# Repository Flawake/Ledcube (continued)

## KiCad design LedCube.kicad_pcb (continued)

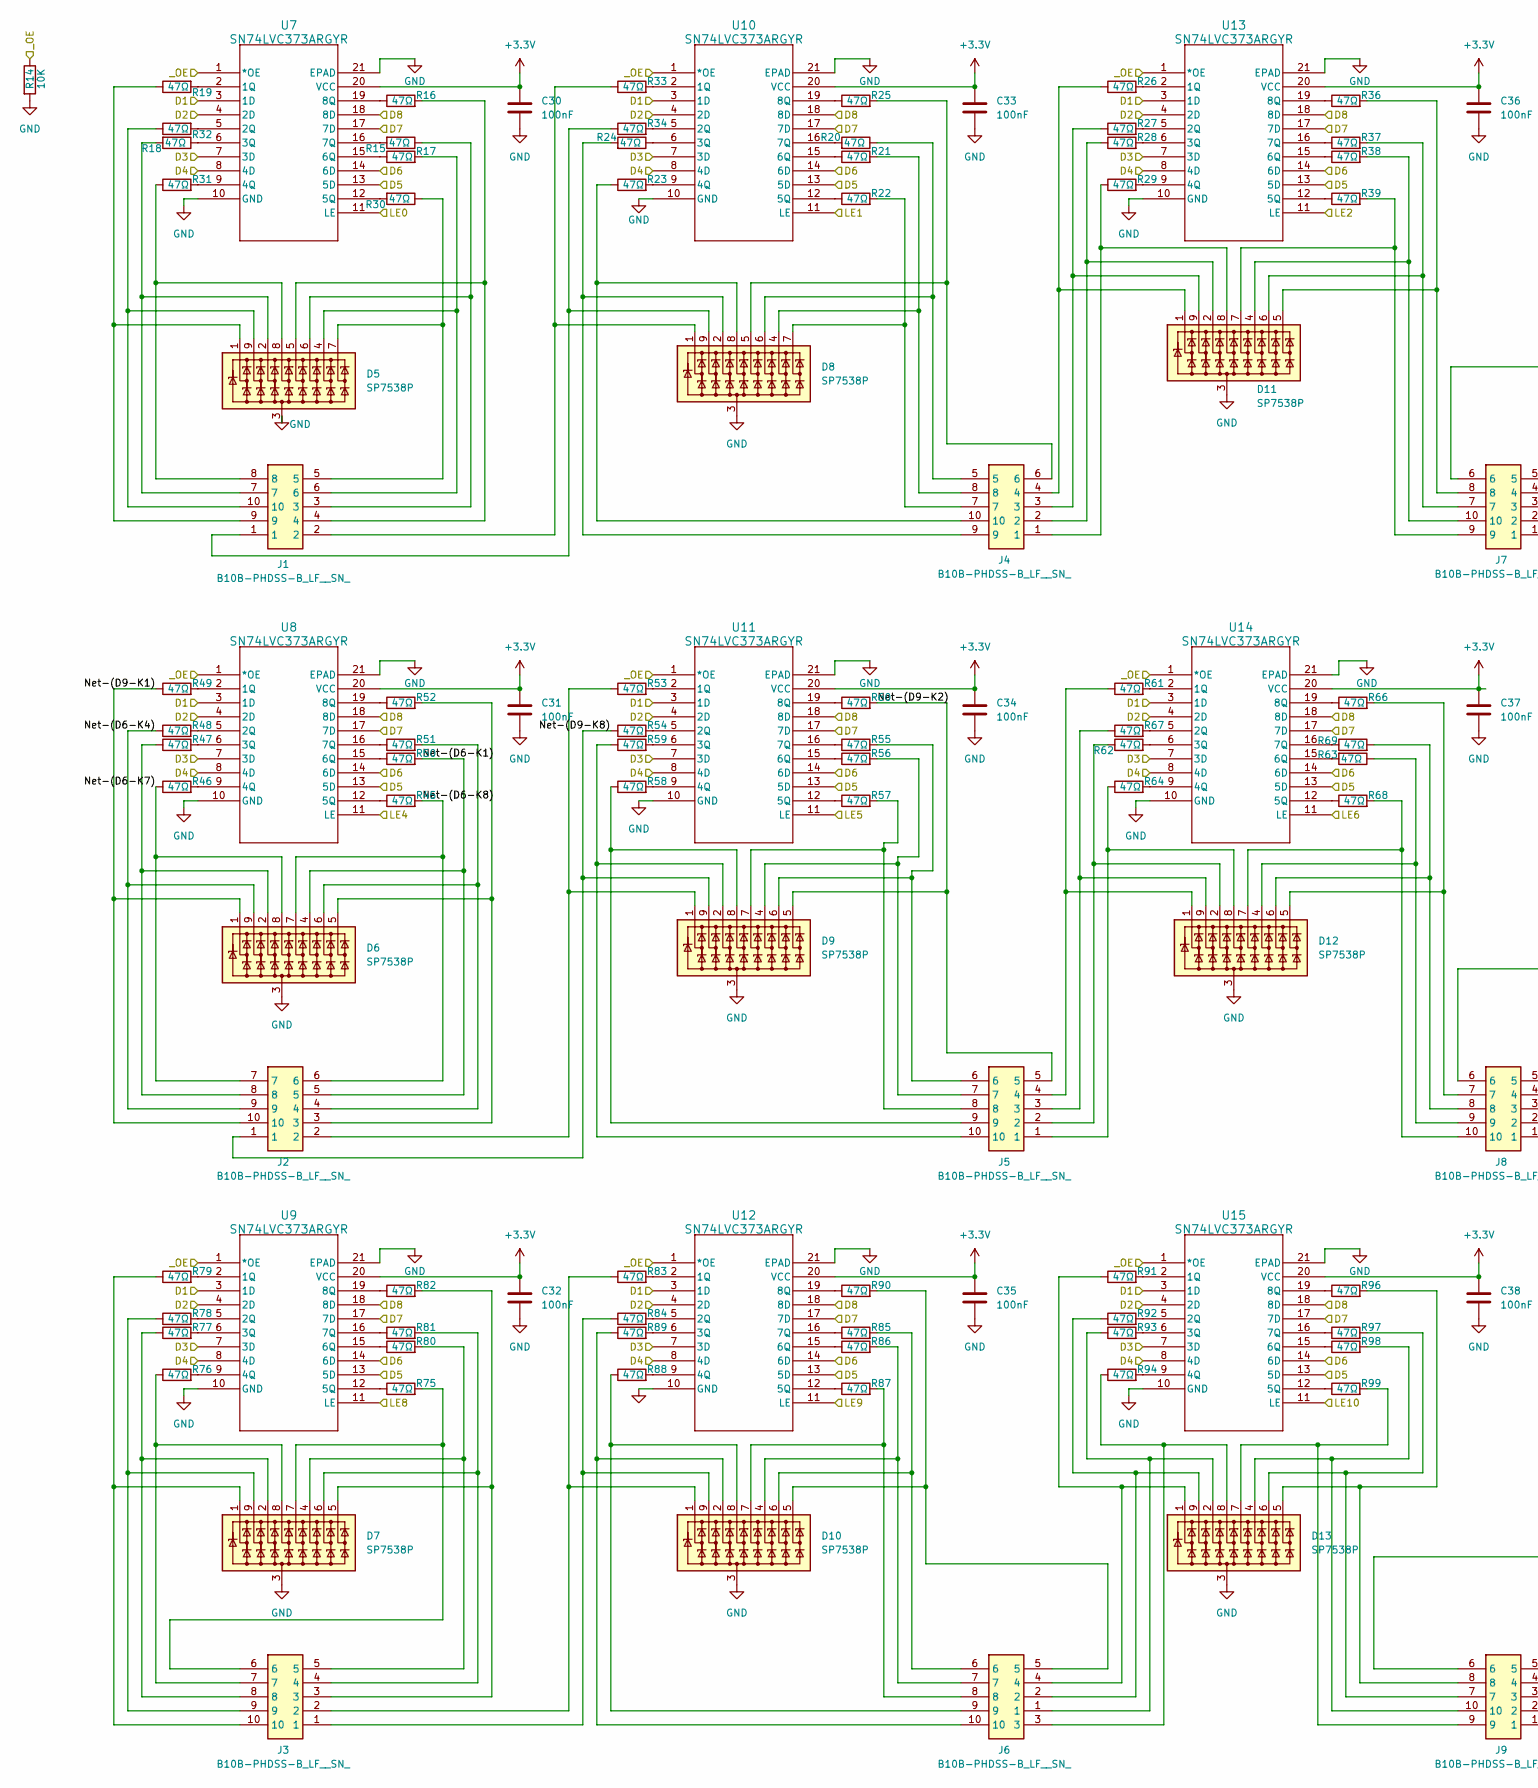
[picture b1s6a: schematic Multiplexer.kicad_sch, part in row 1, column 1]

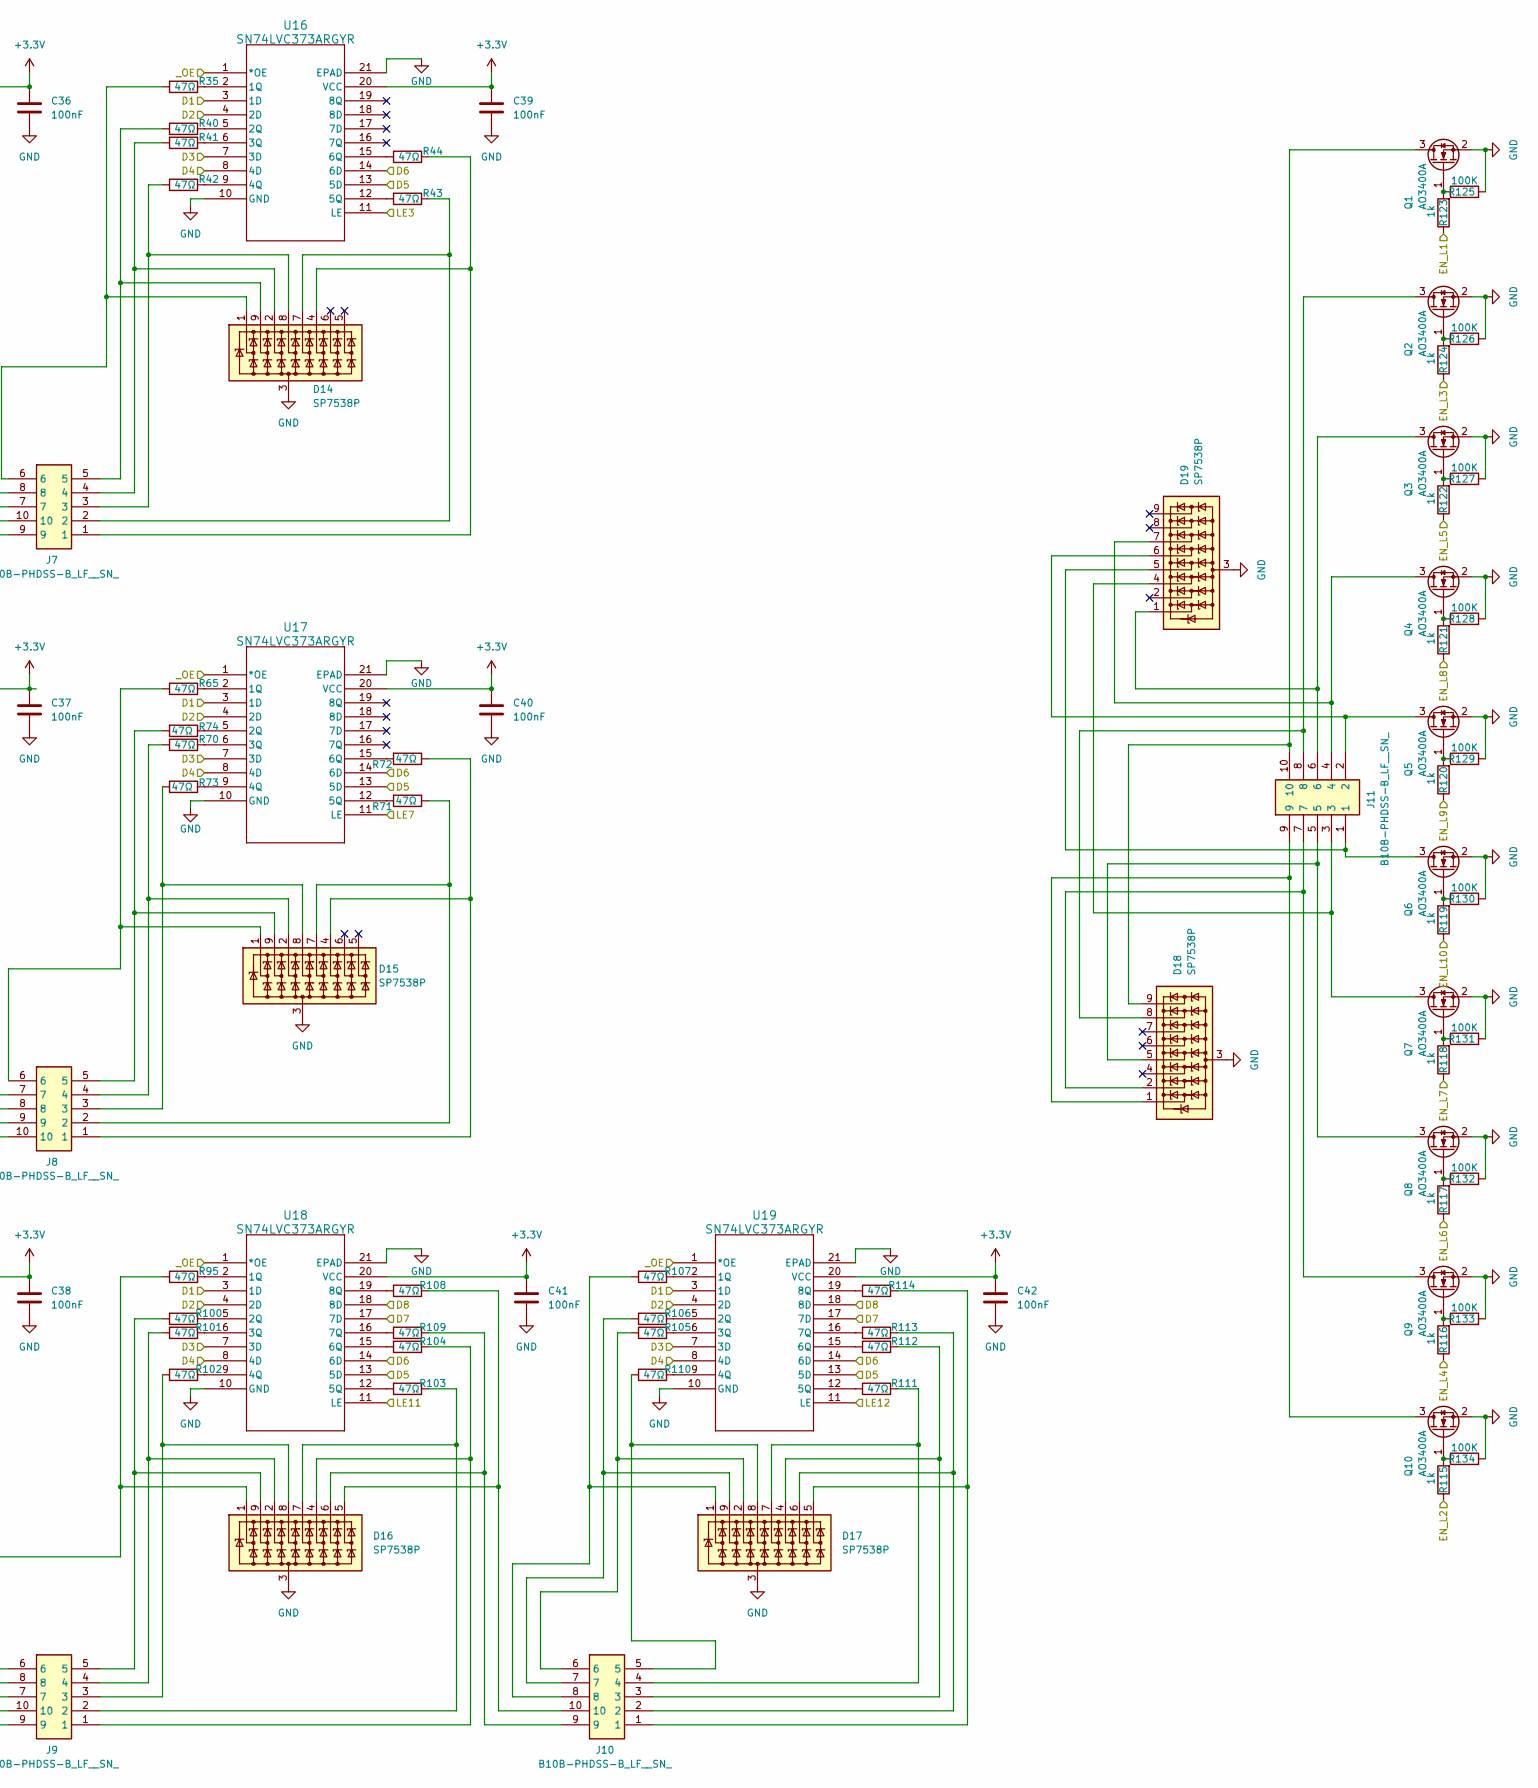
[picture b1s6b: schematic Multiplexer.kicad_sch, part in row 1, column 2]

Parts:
C30, C31, C32, C33, C34, C35, C36, C37, C38, C39, C40, C41, C42: 100nF; C_0603_1608Metric; LCSC C282519
D5, D6, D7, D8, D9, D10, D11, D12, D13, D14, D15, D16, D17, D18, D19: SP7538P; UDFN-9_1.0x3.8mm_P0.5mm
J1, J2, J3, J4, J5, J6, J7, J8, J9, J10, J11: B10B-PHDSS-B_LF__SN_; B10BPHDSSBLFSN; Mouser Part Number 306-B10BPHDSSBLFSN
Q1, Q2, Q3, Q4, Q5, Q6, Q7, Q8, Q9, Q10: AO3400A; SOT-23
R14: 10K; R_0603_1608Metric; LCSC C25804
R15, R16, R17, R18, R19, R20, R21, R22, R23, R24, R25, R26, R27, R28, R29, R30, R31, R32, R33, R34, R35, R36, R37, R38, R39, R40, R41, R42, R43, R44, R45, R46, R47, R48, R49, R50, R51, R52, R53, R54, R55, R56, R57, R58, R59, R60, R61, R62, R63, R64, R65, R66, R67, R68, R69, R70, R71, R72, R73, R74, R75, R76, R77, R78, R79, R80, R81, R82, R83, R84, R85, R86, R87, R88, R89, R90, R91, R92, R93, R94, R95, R96, R97, R98, R99, R100, R101, R102, R103, R104, R105, R106, R107, R108, R109, R110, R111, R112, R113, R114: 47Ω; R_0603_1608Metric; LCSC C23182
R115, R116, R117, R118, R119, R120, R121, R122, R123, R124: 1k; R_0603_1608Metric; LCSC C22548
R125, R126, R127, R128, R129, R130, R131, R132, R133, R134: 100K; R_0603_1608Metric; LCSC C25803
U7, U8, U9, U10, U11, U12, U13, U14, U15, U16, U17, U18, U19: SN74LVC373ARGYR; RGY20_3P05X2P05

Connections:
+3.3V: C30.1, C31.1, C32.1, C33.1, C34.1, C35.1, C36.1, C37.1, C38.1, C39.1, C40.1, C41.1, C42.1, U7.20 (VCC), U8.20 (VCC), U9.20 (VCC), U10.20 (VCC), U11.20 (VCC), U12.20 (VCC), U13.20 (VCC), U14.20 (VCC), U15.20 (VCC), U16.20 (VCC), U17.20 (VCC), U18.20 (VCC), U19.20 (VCC); also elsewhere on the board
/Core/D1: U7.3 (1D), U8.3 (1D), U9.3 (1D), U10.3 (1D), U11.3 (1D), U12.3 (1D), U13.3 (1D), U14.3 (1D), U15.3 (1D), U16.3 (1D), U17.3 (1D), U18.3 (1D), U19.3 (1D); also elsewhere on the board
/Core/D2: U7.4 (2D), U8.4 (2D), U9.4 (2D), U10.4 (2D), U11.4 (2D), U12.4 (2D), U13.4 (2D), U14.4 (2D), U15.4 (2D), U16.4 (2D), U17.4 (2D), U18.4 (2D), U19.4 (2D); also elsewhere on the board
/Core/D3: U7.7 (3D), U8.7 (3D), U9.7 (3D), U10.7 (3D), U11.7 (3D), U12.7 (3D), U13.7 (3D), U14.7 (3D), U15.7 (3D), U16.7 (3D), U17.7 (3D), U18.7 (3D), U19.7 (3D); also elsewhere on the board
/Core/D4: U7.8 (4D), U8.8 (4D), U9.8 (4D), U10.8 (4D), U11.8 (4D), U12.8 (4D), U13.8 (4D), U14.8 (4D), U15.8 (4D), U16.8 (4D), U17.8 (4D), U18.8 (4D), U19.8 (4D); also elsewhere on the board
/Core/D5: U7.13 (5D), U8.13 (5D), U9.13 (5D), U10.13 (5D), U11.13 (5D), U12.13 (5D), U13.13 (5D), U14.13 (5D), U15.13 (5D), U16.13 (5D), U17.13 (5D), U18.13 (5D), U19.13 (5D); also elsewhere on the board
/Core/D6: U7.14 (6D), U8.14 (6D), U9.14 (6D), U10.14 (6D), U11.14 (6D), U12.14 (6D), U13.14 (6D), U14.14 (6D), U15.14 (6D), U16.14 (6D), U17.14 (6D), U18.14 (6D), U19.14 (6D); also elsewhere on the board
/Core/D7: U7.17 (7D), U8.17 (7D), U9.17 (7D), U10.17 (7D), U11.17 (7D), U12.17 (7D), U13.17 (7D), U14.17 (7D), U15.17 (7D), U18.17 (7D), U19.17 (7D); also elsewhere on the board
/Core/D8: U7.18 (8D), U8.18 (8D), U9.18 (8D), U10.18 (8D), U11.18 (8D), U12.18 (8D), U13.18 (8D), U14.18 (8D), U15.18 (8D), U18.18 (8D), U19.18 (8D); also elsewhere on the board
/Core/EN_L1: R123.1; also elsewhere on the board
/Core/EN_L2: R115.1; also elsewhere on the board
/Core/EN_L3: R124.1; also elsewhere on the board
/Core/EN_L4: R116.1; also elsewhere on the board
/Core/EN_L5: R122.1; also elsewhere on the board
/Core/EN_L6: R117.1; also elsewhere on the board
/Core/EN_L7: R118.1; also elsewhere on the board
/Core/EN_L8: R121.1; also elsewhere on the board
/Core/EN_L9: R120.1; also elsewhere on the board
/Core/EN_L10: R119.1; also elsewhere on the board
/Core/LE0: U7.11 (LE); also elsewhere on the board
/Core/LE1: U10.11 (LE); also elsewhere on the board
/Core/LE2: U13.11 (LE); also elsewhere on the board
/Core/LE3: U16.11 (LE); also elsewhere on the board
/Core/LE4: U8.11 (LE); also elsewhere on the board
/Core/LE5: U11.11 (LE); also elsewhere on the board
/Core/LE6: U14.11 (LE); also elsewhere on the board
/Core/LE7: U17.11 (LE); also elsewhere on the board
/Core/LE8: U9.11 (LE); also elsewhere on the board
/Core/LE9: U12.11 (LE); also elsewhere on the board
/Core/LE10: U15.11 (LE); also elsewhere on the board
/Core/LE11: U18.11 (LE); also elsewhere on the board
/Core/LE12: U19.11 (LE); also elsewhere on the board
/Core/_OE: R14.1, U7.1 (*OE), U8.1 (*OE), U9.1 (*OE), U10.1 (*OE), U11.1 (*OE), U12.1 (*OE), U13.1 (*OE), U14.1 (*OE), U15.1 (*OE), U16.1 (*OE), U17.1 (*OE), U18.1 (*OE), U19.1 (*OE); also elsewhere on the board
/Multiplexer/Net-(D6-K1): D6.4 (K3), J2.5, R50.2
/Multiplexer/Net-(D6-K4): D6.9 (K8), J2.9, R48.1
/Multiplexer/Net-(D6-K7): D6.8 (K7), J2.7, R46.1
/Multiplexer/Net-(D6-K8): D6.7 (K6), J2.6, R45.2
/Multiplexer/Net-(D9-K1): D6.1 (K1), J2.10, R49.1
/Multiplexer/Net-(D9-K2): D9.5 (K4), J5.5, R60.2
/Multiplexer/Net-(D9-K8): D9.9 (K8), J2.1, R54.1
GND: C30.2, C31.2, C32.2, C33.2, C34.2, C35.2, C36.2, C37.2, C38.2, C39.2, C40.2, C41.2, C42.2, D5.3 (A), D6.3 (A), D7.3 (A), D8.3 (A), D9.3 (A), D10.3 (A), D11.3 (A), D12.3 (A), D13.3 (A), D14.3 (A), D15.3 (A), D16.3 (A), D17.3 (A), D18.3 (A), D19.3 (A), Q1.2 (S), Q2.2 (S), Q3.2 (S), Q4.2 (S), Q5.2 (S), Q6.2 (S), Q7.2 (S), Q8.2 (S), Q9.2 (S), Q10.2 (S), R14.2, R125.2, R126.2, R127.2, R128.2, R129.2, R130.2, R131.2, R132.2, R133.2, R134.2, U7.10 (GND), U7.21 (EPAD), U8.10 (GND), U8.21 (EPAD), U9.10 (GND), U9.21 (EPAD), U10.10 (GND), U10.21 (EPAD), U11.10 (GND), U11.21 (EPAD), U12.10 (GND), U12.21 (EPAD), U13.10 (GND), U13.21 (EPAD), U14.10 (GND), U14.21 (EPAD), U15.10 (GND), U15.21 (EPAD), U16.10 (GND), U16.21 (EPAD), U17.10 (GND), U17.21 (EPAD), U18.10 (GND), U18.21 (EPAD), U19.10 (GND), U19.21 (EPAD); also elsewhere on the board
unnamed: D5.1 (K1), J1.9, R19.1
unnamed: D5.2 (K2), J1.7, R18.2
unnamed: D5.4 (K3), J1.6, R17.2
unnamed: D5.5 (K4), J1.4, R16.2
unnamed: D5.6 (K5), J1.3, R15.1
unnamed: D5.7 (K6), J1.5, R30.1
unnamed: D5.8 (K7), J1.8, R31.1
unnamed: D5.9 (K8), J1.10, R32.1
unnamed: D6.2 (K2), J2.8, R47.1
unnamed: D6.5 (K4), J2.3, R52.2
unnamed: D6.6 (K5), J2.4, R51.2
unnamed: D7.1 (K1), J3.10, R79.1
unnamed: D7.2 (K2), J3.8, R77.1
unnamed: D7.4 (K3), J3.5, R80.2
unnamed: D7.5 (K4), J3.3, R82.2
unnamed: D7.6 (K5), J3.4, R81.2
unnamed: D7.7 (K6), J3.6, R75.2
unnamed: D7.8 (K7), J3.7, R76.1
unnamed: D7.9 (K8), J3.9, R78.1
unnamed: D8.1 (K1), J1.2, R33.1
unnamed: D8.2 (K2), J4.9, R24.2
unnamed: D8.4 (K3), J4.8, R21.2
unnamed: D8.5 (K4), J4.6, R25.2
unnamed: D8.6 (K5), J4.5, R20.1
unnamed: D8.7 (K6), J4.7, R22.2
unnamed: D8.8 (K7), J4.10, R23.1
unnamed: D8.9 (K8), J1.1, R34.1
unnamed: D9.1 (K1), J2.2, R53.1
unnamed: D9.2 (K2), J5.10, R59.1
unnamed: D9.4 (K3), J5.7, R56.2
unnamed: D9.6 (K5), J5.6, R55.2
unnamed: D9.7 (K6), J5.8, R57.2
unnamed: D9.8 (K7), J5.9, R58.1
unnamed: D10.1 (K1), J3.2, R83.1
unnamed: D10.2 (K2), J6.10, R89.1
unnamed: D10.4 (K3), J6.7, R86.2
unnamed: D10.5 (K4), J6.5, R90.2
unnamed: D10.6 (K5), J6.6, R85.2
unnamed: D10.7 (K6), J6.8, R87.2
unnamed: D10.8 (K7), J6.9, R88.1
unnamed: D10.9 (K8), J3.1, R84.1
unnamed: D11.1 (K1), J4.4, R26.1
unnamed: D11.2 (K2), J4.2, R28.1
unnamed: D11.4 (K3), J7.10, R38.2
unnamed: D11.5 (K4), J7.8, R36.2
unnamed: D11.6 (K5), J7.7, R37.2
unnamed: D11.7 (K6), J7.9, R39.2
unnamed: D11.8 (K7), J4.1, R29.1
unnamed: D11.9 (K8), J4.3, R27.1
unnamed: D12.1 (K1), J5.4, R61.1
unnamed: D12.2 (K2), J5.2, R62.1
unnamed: D12.4 (K3), J8.9, R63.1
unnamed: D12.5 (K4), J8.7, R66.2
unnamed: D12.6 (K5), J8.8, R69.2
unnamed: D12.7 (K6), J8.10, R68.2
unnamed: D12.8 (K7), J5.1, R64.1
unnamed: D12.9 (K8), J5.3, R67.1
unnamed: D13.1 (K1), J6.4, R91.1
unnamed: D13.2 (K2), J6.1, R93.1
unnamed: D13.4 (K3), J9.10, R98.2
unnamed: D13.5 (K4), J9.8, R96.2
unnamed: D13.6 (K5), J9.7, R97.2
unnamed: D13.7 (K6), J9.9, R99.2
unnamed: D13.8 (K7), J6.3, R94.1
unnamed: D13.9 (K8), J6.2, R92.1
unnamed: D14.1 (K1), J7.6, R35.1
unnamed: D14.2 (K2), J7.4, R41.1
unnamed: D14.4 (K3), J7.1, R44.2
unnamed: D14.7 (K6), J7.2, R43.2
unnamed: D14.8 (K7), J7.3, R42.1
unnamed: D14.9 (K8), J7.5, R40.1
unnamed: D15.1 (K1), J8.6, R65.1
unnamed: D15.2 (K2), J8.4, R70.1
unnamed: D15.4 (K3), J8.1, R72.1
unnamed: D15.7 (K6), J8.2, R71.1
unnamed: D15.8 (K7), J8.3, R73.2
unnamed: D15.9 (K8), J8.5, R74.2
unnamed: D16.1 (K1), J9.6, R95.1
unnamed: D16.2 (K2), J9.4, R101.1
unnamed: D16.4 (K3), J9.1, R104.2
unnamed: D16.5 (K4), J10.10, R108.2
unnamed: D16.6 (K5), J10.9, R109.2
unnamed: D16.7 (K6), J9.2, R103.2
unnamed: D16.8 (K7), J9.3, R102.1
unnamed: D16.9 (K8), J9.5, R100.1
unnamed: D17.1 (K1), J10.8, R107.1
unnamed: D17.2 (K2), J10.6, R105.1
unnamed: D17.4 (K3), J10.3, R112.2
unnamed: D17.5 (K4), J10.1, R114.2
unnamed: D17.6 (K5), J10.2, R113.2
unnamed: D17.7 (K6), J10.4, R111.2
unnamed: D17.8 (K7), J10.5, R110.1
unnamed: D17.9 (K8), J10.7, R106.1
unnamed: D18.1 (K1), J11.9, Q10.3 (D)
unnamed: D18.2 (K2), J11.7, Q9.3 (D)
unnamed: D18.5 (K4), J11.5, Q8.3 (D)
unnamed: D18.8 (K7), J11.8, Q2.3 (D)
unnamed: D18.9 (K8), J11.10, Q1.3 (D)
unnamed: D19.1 (K1), J11.6, Q3.3 (D)
unnamed: D19.4 (K3), J11.3, Q7.3 (D)
unnamed: D19.5 (K4), J11.1, Q6.3 (D)
unnamed: D19.6 (K5), J11.2, Q5.3 (D)
unnamed: D19.7 (K6), J11.4, Q4.3 (D)
unnamed: Q1.1 (G), R123.2, R125.1
unnamed: Q2.1 (G), R124.2, R126.1
unnamed: Q3.1 (G), R122.2, R127.1
unnamed: Q4.1 (G), R121.2, R128.1
unnamed: Q5.1 (G), R120.2, R129.1
unnamed: Q6.1 (G), R119.2, R130.1
unnamed: Q7.1 (G), R118.2, R131.1
unnamed: Q8.1 (G), R117.2, R132.1
unnamed: Q9.1 (G), R116.2, R133.1
unnamed: Q10.1 (G), R115.2, R134.1
unnamed: R19.2, U7.2 (1Q)
unnamed: R32.2, U7.5 (2Q)
unnamed: R18.1, U7.6 (3Q)
unnamed: R31.2, U7.9 (4Q)
unnamed: R30.2, U7.12 (5Q)
unnamed: R17.1, U7.15 (6Q)
unnamed: R15.2, U7.16 (7Q)
unnamed: R16.1, U7.19 (8Q)
unnamed: R49.2, U8.2 (1Q)
unnamed: R48.2, U8.5 (2Q)
unnamed: R47.2, U8.6 (3Q)
unnamed: R46.2, U8.9 (4Q)
unnamed: R45.1, U8.12 (5Q)
unnamed: R50.1, U8.15 (6Q)
unnamed: R51.1, U8.16 (7Q)
unnamed: R52.1, U8.19 (8Q)
unnamed: R79.2, U9.2 (1Q)
unnamed: R78.2, U9.5 (2Q)
unnamed: R77.2, U9.6 (3Q)
unnamed: R76.2, U9.9 (4Q)
unnamed: R75.1, U9.12 (5Q)
unnamed: R80.1, U9.15 (6Q)
unnamed: R81.1, U9.16 (7Q)
unnamed: R82.1, U9.19 (8Q)
unnamed: R33.2, U10.2 (1Q)
unnamed: R34.2, U10.5 (2Q)
unnamed: R24.1, U10.6 (3Q)
unnamed: R23.2, U10.9 (4Q)
unnamed: R22.1, U10.12 (5Q)
unnamed: R21.1, U10.15 (6Q)
unnamed: R20.2, U10.16 (7Q)
unnamed: R25.1, U10.19 (8Q)
unnamed: R53.2, U11.2 (1Q)
unnamed: R54.2, U11.5 (2Q)
unnamed: R59.2, U11.6 (3Q)
unnamed: R58.2, U11.9 (4Q)
unnamed: R57.1, U11.12 (5Q)
unnamed: R56.1, U11.15 (6Q)
unnamed: R55.1, U11.16 (7Q)
unnamed: R60.1, U11.19 (8Q)
unnamed: R83.2, U12.2 (1Q)
unnamed: R84.2, U12.5 (2Q)
unnamed: R89.2, U12.6 (3Q)
unnamed: R88.2, U12.9 (4Q)
unnamed: R87.1, U12.12 (5Q)
unnamed: R86.1, U12.15 (6Q)
unnamed: R85.1, U12.16 (7Q)
unnamed: R90.1, U12.19 (8Q)
unnamed: R26.2, U13.2 (1Q)
unnamed: R27.2, U13.5 (2Q)
unnamed: R28.2, U13.6 (3Q)
unnamed: R29.2, U13.9 (4Q)
unnamed: R39.1, U13.12 (5Q)
unnamed: R38.1, U13.15 (6Q)
unnamed: R37.1, U13.16 (7Q)
unnamed: R36.1, U13.19 (8Q)
unnamed: R61.2, U14.2 (1Q)
unnamed: R67.2, U14.5 (2Q)
unnamed: R62.2, U14.6 (3Q)
unnamed: R64.2, U14.9 (4Q)
unnamed: R68.1, U14.12 (5Q)
unnamed: R63.2, U14.15 (6Q)
unnamed: R69.1, U14.16 (7Q)
unnamed: R66.1, U14.19 (8Q)
unnamed: R91.2, U15.2 (1Q)
unnamed: R92.2, U15.5 (2Q)
unnamed: R93.2, U15.6 (3Q)
unnamed: R94.2, U15.9 (4Q)
unnamed: R99.1, U15.12 (5Q)
unnamed: R98.1, U15.15 (6Q)
unnamed: R97.1, U15.16 (7Q)
unnamed: R96.1, U15.19 (8Q)
unnamed: R35.2, U16.2 (1Q)
unnamed: R40.2, U16.5 (2Q)
unnamed: R41.2, U16.6 (3Q)
unnamed: R42.2, U16.9 (4Q)
unnamed: R43.1, U16.12 (5Q)
unnamed: R44.1, U16.15 (6Q)
unnamed: R65.2, U17.2 (1Q)
unnamed: R74.1, U17.5 (2Q)
unnamed: R70.2, U17.6 (3Q)
unnamed: R73.1, U17.9 (4Q)
unnamed: R71.2, U17.12 (5Q)
unnamed: R72.2, U17.15 (6Q)
unnamed: R95.2, U18.2 (1Q)
unnamed: R100.2, U18.5 (2Q)
unnamed: R101.2, U18.6 (3Q)
unnamed: R102.2, U18.9 (4Q)
unnamed: R103.1, U18.12 (5Q)
unnamed: R104.1, U18.15 (6Q)
unnamed: R109.1, U18.16 (7Q)
unnamed: R108.1, U18.19 (8Q)
unnamed: R107.2, U19.2 (1Q)
unnamed: R106.2, U19.5 (2Q)
unnamed: R105.2, U19.6 (3Q)
unnamed: R110.2, U19.9 (4Q)
unnamed: R111.1, U19.12 (5Q)
unnamed: R112.1, U19.15 (6Q)
unnamed: R113.1, U19.16 (7Q)
unnamed: R114.1, U19.19 (8Q)

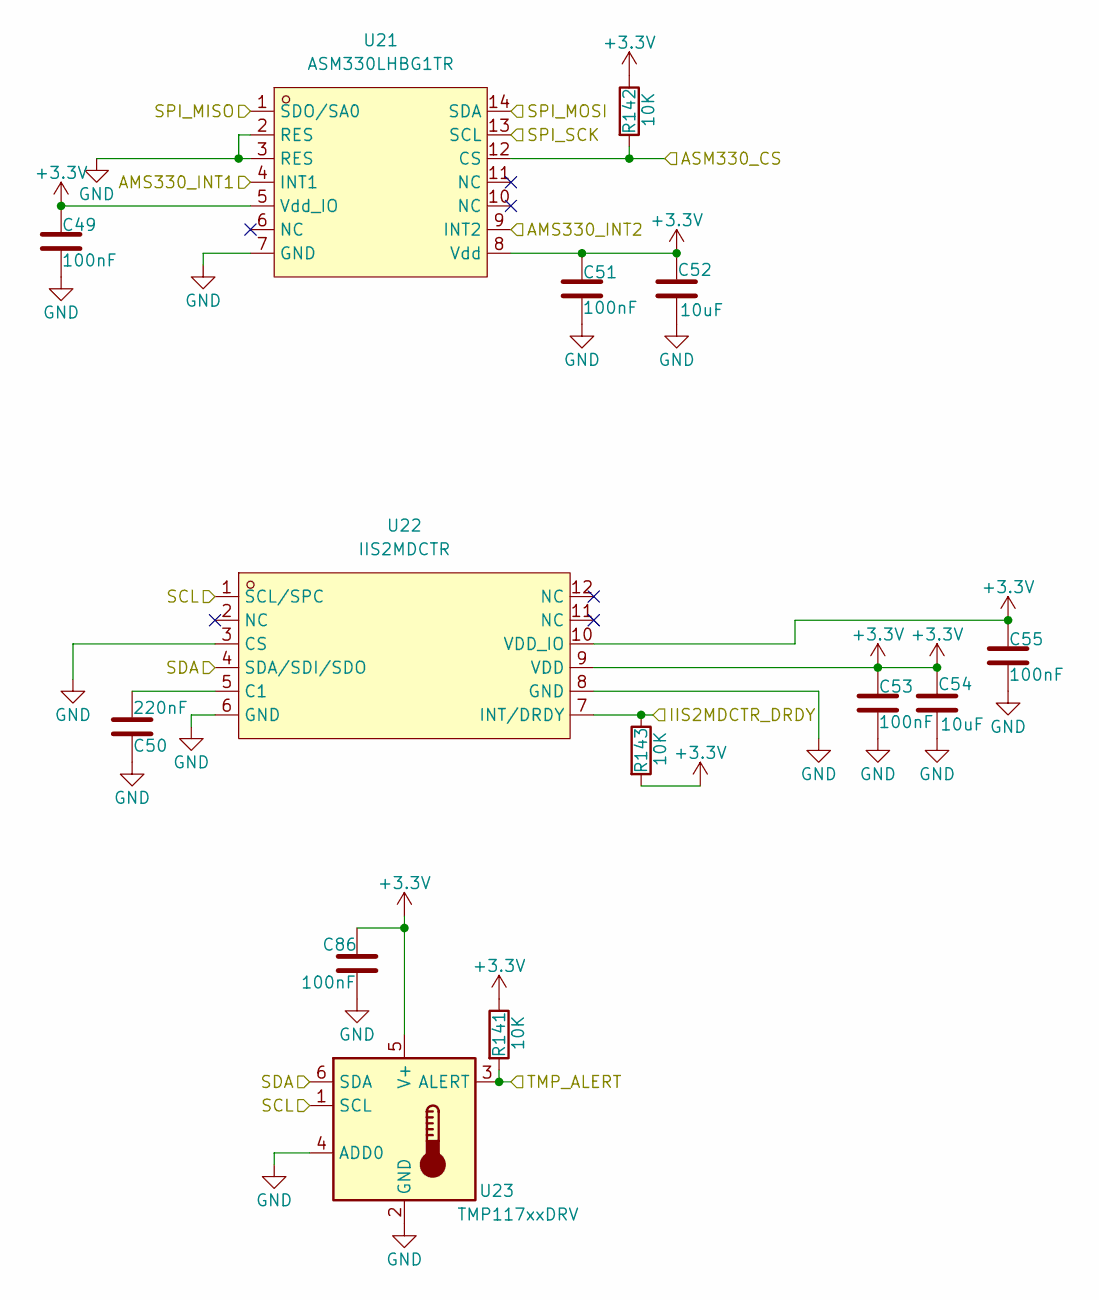
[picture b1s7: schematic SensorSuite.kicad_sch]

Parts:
C49, C51, C53, C55, C86: 100nF; C_0603_1608Metric; LCSC C282519
C50: 220nF; C_0402_1005Metric; LCSC C16772
C52, C54: 10uF; C_0805_2012Metric; LCSC C440198
R141, R142, R143: 10K; R_0603_1608Metric; LCSC C25804
U21: ASM330LHBG1TR; LGA-14_L3.0-W2.5-P0.50-BL; LCSC Part C22458556
U22: IIS2MDCTR; LGA-12_L2.0-W2.0-P0.50-TL; LCSC Part C2655002
U23: TMP117xxDRV; WSON-6-1EP_2x2mm_P0.65mm_EP1x1.6mm

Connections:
+3.3V: C49.1, C51.1, C52.1, C53.1, C54.1, C55.1, C86.1, R141.1, R142.1, R143.2, U21.5 (Vdd_IO), U21.8 (Vdd), U22.9 (VDD), U22.10 (VDD_IO), U23.5 (V+); also elsewhere on the board
/Core/AMS330_CS: R142.2, U21.12 (CS); also elsewhere on the board
/Core/AMS330_INT1: U21.4 (INT1); also elsewhere on the board
/Core/AMS330_INT2: U21.9 (INT2); also elsewhere on the board
/Core/I2C1_SCL: U22.1 (SCL/SPC), U23.1 (SCL); also elsewhere on the board
/Core/I2C1_SDA: U22.4 (SDA/SDI/SDO), U23.6 (SDA); also elsewhere on the board
/Core/IIS2MDCTR_DRDY: R143.1, U22.7 (INT/DRDY); also elsewhere on the board
/Core/SPI1_MISO: U21.1 (SDO/SA0); also elsewhere on the board
/Core/SPI1_MOSI: U21.14 (SDA); also elsewhere on the board
/Core/SPI1_SCK: U21.13 (SCL); also elsewhere on the board
/Core/TMP_ALERT: R141.2, U23.3 (ALERT); also elsewhere on the board
GND: C49.2, C50.2, C51.2, C52.2, C53.2, C54.2, C55.2, C86.2, U21.2 (RES), U21.3 (RES), U21.7 (GND), U22.3 (CS), U22.6 (GND), U22.8 (GND), U23.2 (GND), U23.4 (ADD0); also elsewhere on the board
unnamed: C50.1, U22.5 (C1)

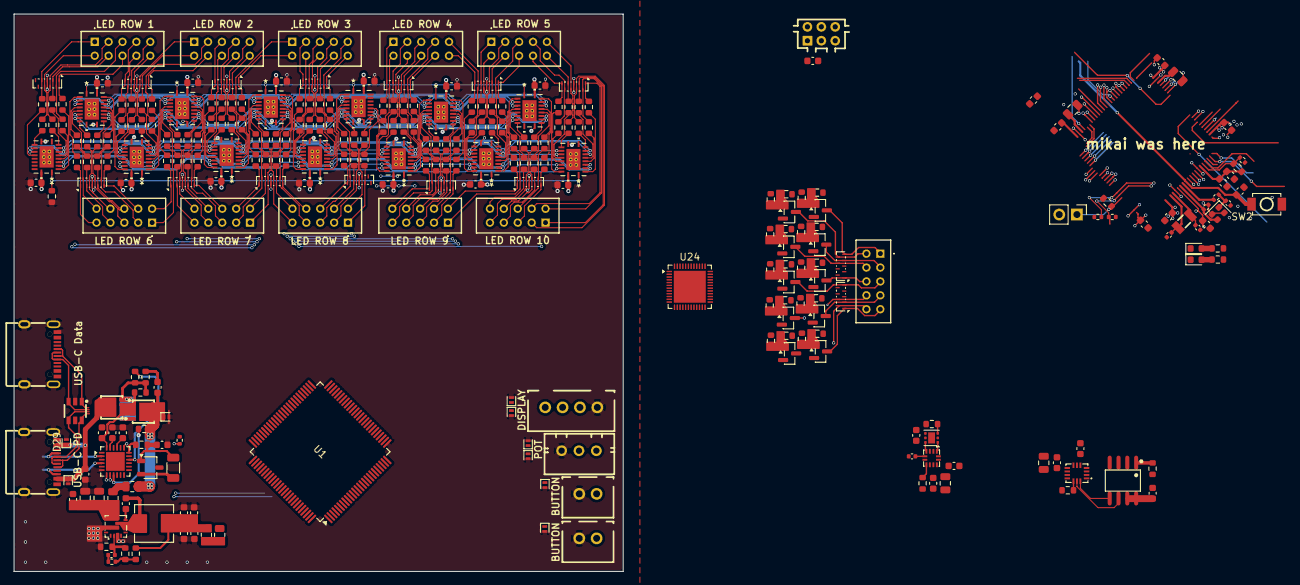
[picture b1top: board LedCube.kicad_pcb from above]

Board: 4 copper layers, 87.7 x 80.2 mm, 287 parts (1 on the bottom side), 315 nets.

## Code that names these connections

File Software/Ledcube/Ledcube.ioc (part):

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Mcu.Name=STM32H743VGTx
Mcu.Package=LQFP100
Mcu.UserName=STM32H743VGTx
PA0.GPIOParameters=GPIO_Label
PA0.GPIO_Label=GDO0_1
PA0.Signal=GPIO_Input
PA1.GPIOParameters=GPIO_Label
PA1.GPIO_Label=GDO2_1
PA1.Signal=GPIO_Input
PA10.GPIOParameters=GPIO_Label
PA10.GPIO_Label=MUX_OE
PA10.Signal=GPIO_Output
PA11.Mode=Device_Only
PA11.Signal=USB_OTG_FS_DM
PA12.Mode=Device_Only
PA12.Signal=USB_OTG_FS_DP
PA15\ (JTDI).GPIOParameters=GPIO_Label
PA15\ (JTDI).GPIO_Label=LE0
PA15\ (JTDI).Signal=GPIO_Output
PA2.GPIOParameters=GPIO_Label
PA2.GPIO_Label=GDO0_2
PA2.Signal=GPIO_Input
PA3.GPIOParameters=GPIO_Label
PA3.GPIO_Label=GDO2_2
PA3.Signal=GPIO_Input
PA4.GPIOParameters=GPIO_Label
PA4.GPIO_Label=MEM_WE
PA4.Signal=GPIO_Output
PA5.GPIOParameters=GPIO_Label
PA5.GPIO_Label=MEM_CS
PA5.Signal=GPIO_Output
PA6.Mode=Full_Duplex_Master
PA6.Signal=SPI1_MISO
PA7.Mode=Full_Duplex_Master
PA7.Signal=SPI1_MOSI
PA8.GPIOParameters=GPIO_Label
PA8.GPIO_Label=MUX_D2
PA8.Signal=GPIO_Output
PA9.GPIOParameters=GPIO_Label
PA9.GPIO_Label=MUX_D1
PA9.Signal=GPIO_Output
PB0.GPIOParameters=GPIO_Label
PB0.GPIO_Label=AMS330_INT2
PB0.Signal=GPIO_Input
PB1.GPIOParameters=GPIO_Label
PB1.GPIO_Label=POTMETER
PB1.Signal=ADCx_INP5
PB10.Mode=Full_Duplex_Master
PB10.Signal=SPI2_SCK
PB11.GPIOParameters=GPIO_Label
PB11.GPIO_Label=EN_L8
PB11.Signal=GPIO_Output
PB12.GPIOParameters=GPIO_Label
PB12.GPIO_Label=EN_L7
PB12.Signal=GPIO_Output
PB13.GPIOParameters=GPIO_Label
PB13.GPIO_Label=EN_L6
PB13.Signal=GPIO_Output
PB14.Mode=Device_Only_FS
PB14.Signal=USB_OTG_HS_DM
PB15.Mode=Device_Only_FS
PB15.Signal=USB_OTG_HS_DP
PB3\ (JTDO/TRACESWO).Mode=Full_Duplex_Master
PB3\ (JTDO/TRACESWO).Signal=SPI1_SCK
PB4\ (NJTRST).GPIOParameters=GPIO_Label
PB4\ (NJTRST).GPIO_Label=IIS2MDCTR_DRDY
PB4\ (NJTRST).Signal=GPIO_Input
PB5.GPIOParameters=GPIO_Label
PB5.GPIO_Label=STUSB4500_ALERT
PB5.Signal=GPIO_Input
PB6.Mode=I2C
PB6.Signal=I2C1_SCL
PB7.Mode=I2C
PB7.Signal=I2C1_SDA
PC0.GPIOParameters=GPIO_Label
PC0.GPIO_Label=BLE_SPI_CS_1
PC0.Signal=GPIO_Output
PC1.Mode=Full_Duplex_Master
PC1.Signal=SPI2_MOSI
PC10.GPIOParameters=GPIO_Label
PC10.GPIO_Label=LE1
PC10.Signal=GPIO_Output
PC11.GPIOParameters=GPIO_Label
PC11.GPIO_Label=LE2
PC11.Signal=GPIO_Output
PC12.GPIOParameters=GPIO_Label
PC12.GPIO_Label=LE3
PC12.Signal=GPIO_Output
PC14-OSC32_IN\ (OSC32_IN).Mode=LSE-External-Oscillator
PC14-OSC32_IN\ (OSC32_IN).Signal=RCC_OSC32_IN
PC15-OSC32_OUT\ (OSC32_OUT).Mode=LSE-External-Oscillator
PC15-OSC32_OUT\ (OSC32_OUT).Signal=RCC_OSC32_OUT
PC2_C.Mode=Full_Duplex_Master
PC2_C.Signal=SPI2_MISO
PC3_C.GPIOParameters=GPIO_Label
PC3_C.GPIO_Label=BLE_SPI_CS_2
PC3_C.Signal=GPIO_Output
PC4.GPIOParameters=GPIO_Label
PC4.GPIO_Label=AMS330_CS
PC4.Signal=GPIO_Output
PC5.GPIOParameters=GPIO_Label
PC5.GPIO_Label=AMS330_INT1
PC5.Signal=GPIO_Input
PC6.GPIOParameters=GPIO_Label
PC6.GPIO_Label=MUX_D6
PC6.Signal=GPIO_Output
PC7.GPIOParameters=GPIO_Label
PC7.GPIO_Label=MUX_D5
PC7.Signal=GPIO_Output
PC8.GPIOParameters=GPIO_Label
PC8.GPIO_Label=MUX_D4
PC8.Signal=GPIO_Output
PC9.GPIOParameters=GPIO_Label
PC9.GPIO_Label=MUX_D3
PC9.Signal=GPIO_Output
PD0.GPIOParameters=GPIO_Label
PD0.GPIO_Label=LE4
PD0.Signal=GPIO_Output
PD1.GPIOParameters=GPIO_Label
PD1.GPIO_Label=LE5
PD1.Signal=GPIO_Output
PD10.GPIOParameters=GPIO_Label
PD10.GPIO_Label=EN_L3
PD10.Signal=GPIO_Output
PD11.GPIOParameters=GPIO_Label
PD11.GPIO_Label=EN_L2
PD11.Signal=GPIO_Output
PD12.GPIOParameters=GPIO_Label
PD12.GPIO_Label=EN_L1
PD12.Signal=GPIO_Output
PD13.GPIOParameters=GPIO_Label
PD13.GPIO_Label=LE12
PD13.Signal=GPIO_Output
PD14.GPIOParameters=GPIO_Label
PD14.GPIO_Label=MUX_D8
PD14.Signal=GPIO_Output
PD15.GPIOParameters=GPIO_Label
PD15.GPIO_Label=MUX_D7
PD15.Signal=GPIO_Output
PD2.GPIOParameters=GPIO_Label
PD2.GPIO_Label=LE6
PD2.Signal=GPIO_Output
PD3.GPIOParameters=GPIO_Label
PD3.GPIO_Label=LE7
PD3.Signal=GPIO_Output
PD4.GPIOParameters=GPIO_Label
PD4.GPIO_Label=LE8
PD4.Signal=GPIO_Output
PD5.GPIOParameters=GPIO_Label
PD5.GPIO_Label=LE9
PD5.Signal=GPIO_Output
PD6.GPIOParameters=GPIO_Label
PD6.GPIO_Label=LE10
PD6.Signal=GPIO_Output
PD7.GPIOParameters=GPIO_Label
PD7.GPIO_Label=LE11
PD7.Signal=GPIO_Output
PD8.GPIOParameters=GPIO_Label
PD8.GPIO_Label=EN_L5
PD8.Signal=GPIO_Output
PD9.GPIOParameters=GPIO_Label
PD9.GPIO_Label=EN_L4
PD9.Signal=GPIO_Output
PE10.GPIOParameters=GPIO_Label
PE10.GPIO_Label=BUTTON_1
PE10.Signal=GPIO_Input
PE11.GPIOParameters=GPIO_Label
PE11.GPIO_Label=BUTTON_2
PE11.Signal=GPIO_Input
PE13.GPIOParameters=GPIO_Label
PE13.GPIO_Label=TMP_ALERT
PE13.Signal=GPIO_Input
PE14.GPIOParameters=GPIO_Label
PE14.GPIO_Label=EN_L10
PE14.Signal=GPIO_Output
PE15.GPIOParameters=GPIO_Label
PE15.GPIO_Label=EN_L9
PE15.Signal=GPIO_Output
PE4.GPIOParameters=GPIO_Label
PE4.GPIO_Label=STATUS_LED
PE4.Signal=GPIO_Output
PH0-OSC_IN\ (PH0).Mode=HSE-External-Oscillator
PH0-OSC_IN\ (PH0).Signal=RCC_OSC_IN
PH1-OSC_OUT\ (PH1).Mode=HSE-External-Oscillator
PH1-OSC_OUT\ (PH1).Signal=RCC_OSC_OUT
RCC.SYSCLKFreq_VALUE=400000000
RCC.SYSCLKSource=RCC_SYSCLKSOURCE_PLLCLK
board=custom

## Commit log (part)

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2026-02-13 Schematic + PCB
2026-02-13 vibe fix
